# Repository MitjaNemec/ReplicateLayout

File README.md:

# KiCAD Replicate Layout Plugin

> [!NOTE]
> This change ports the plugin to **KiCad 10** (targets KiCad 10.0). KiCad 10
> removed the `pcbnew.ID_V_TOOLBAR` constant the dialog relied on, which made the
> plugin raise on every run (issue #87); this is fixed with a fallback that still
> works on KiCad 9. It has been verified to reproduce the KiCad 9 behaviour exactly
> (see *Testing* below). Similar functionality is also available in KiCad natively;
> see the [official KiCad multichannel documentation](https://docs.kicad.org/10.0/en/pcbnew/pcbnew.html#multichannel).
> The plugin remains useful for replication driven by hierarchical sheets.

The repository includes code for KiCad Action plugin which replicates part of the PCB layout.

Replicate the PCB layout of one hierarchical sheet to other hierarchical sheets. This replication is based upon hierarchical sheets in Eeschema. The basic requirement for replication is that the section to be replicated (source) is completely contained within a single hierarchical sheet, and replicated sections (destination) are just copies of the same sheet. Complex hierarchies are supported and the replicated sheet can contain subsheets. The plugin replicates footprints, zones, tracks, text and drawings.

After the section for replication (source section) has been laid out (footprints, tracks, text objects and zones placed) you need to:
1. Place the anchor footprints for the destination sections you want to replicate. This defines the position and orientation of replicated sections. You can use [the PlaceFootprints action plugin](https://github.com/MitjaNemec/PlaceFootprints) for this.
2. Select the same anchor footprint within the source section.
3. Run the plugin.
4. Choose which hierarchical level you wish to replicate.
5. Select which sheets you want to replicate (default is all of them).
6. Select whether you want to also replicate tracks, zones and/or text objects.
7. Select whether you want to group replicated footprints/tracks/zones/text/drawings by hierarchical sheets.
8. Select whether you want to replicate tracks/zones/text which intersect the pivot bounding box or just those contained within the bounding box.
9. Select whether you want to delete already laid out tracks/zones/text (this is useful when updating an already replicated layout).
10. Hit OK.

By default, only objects which are fully contained in the bounding box constituted by all the footprints in the section will be replicated. You can select to also replicate zones and tracks which intersect this bounding box. Additionally, tracks, text and zones which are already laid out in the replicated bounding boxes can be removed (useful when updating). Note that bounding boxes are squares aligned with the x and y axis, regardless of section orientation.

## Installation

The preferred way to install the plugin is via KiCad's Plugin and Content Manager (PCM). Installation on non-networked devices can be done by downloading [the latest release](https://github.com/MitjaNemec/ReplicateLayout/releases/latest) and installing in the PCM using the `Install from file` option.

## Testing

The plugin ships with a headless, GUI-free test-suite driven entirely through the
pcbnew scripting API (`test_replicate_layout.py`). It runs a number of replication
scenarios (inner/outer hierarchy levels, flipped anchors, "contained" vs.
"intersecting" selection, removal of existing copper, grouping and footprint-text
replication), plus regression tests for issue #86 (already-grouped destination
footprints). Each replication result is checked for **geometric correctness**:
every replicated section must keep the same internal geometry (pairwise distances,
relative orientation and relative flip) as the source section. This check is
independent of any coordinate convention, so it validates the result on its own
merits.

Run it with the Python interpreter bundled with KiCad, for example on macOS:

```bash
/Applications/KiCad/KiCad.app/Contents/Frameworks/Python.framework/Versions/3.9/bin/python3.9 test_replicate_layout.py
```

The suite can additionally compare output against committed reference signatures to
prove byte-for-byte parity with a previous KiCad version: run with `--gen-refs`
under that KiCad (writing `test_refs/*.json`), then a normal run under the new KiCad
verifies the output matches. This is how the KiCad 9 → 10 parity was confirmed.

**Author :** doc.dr. Mitja Nemec
**KiCad 10 port :** 2026
**Date :** 2025

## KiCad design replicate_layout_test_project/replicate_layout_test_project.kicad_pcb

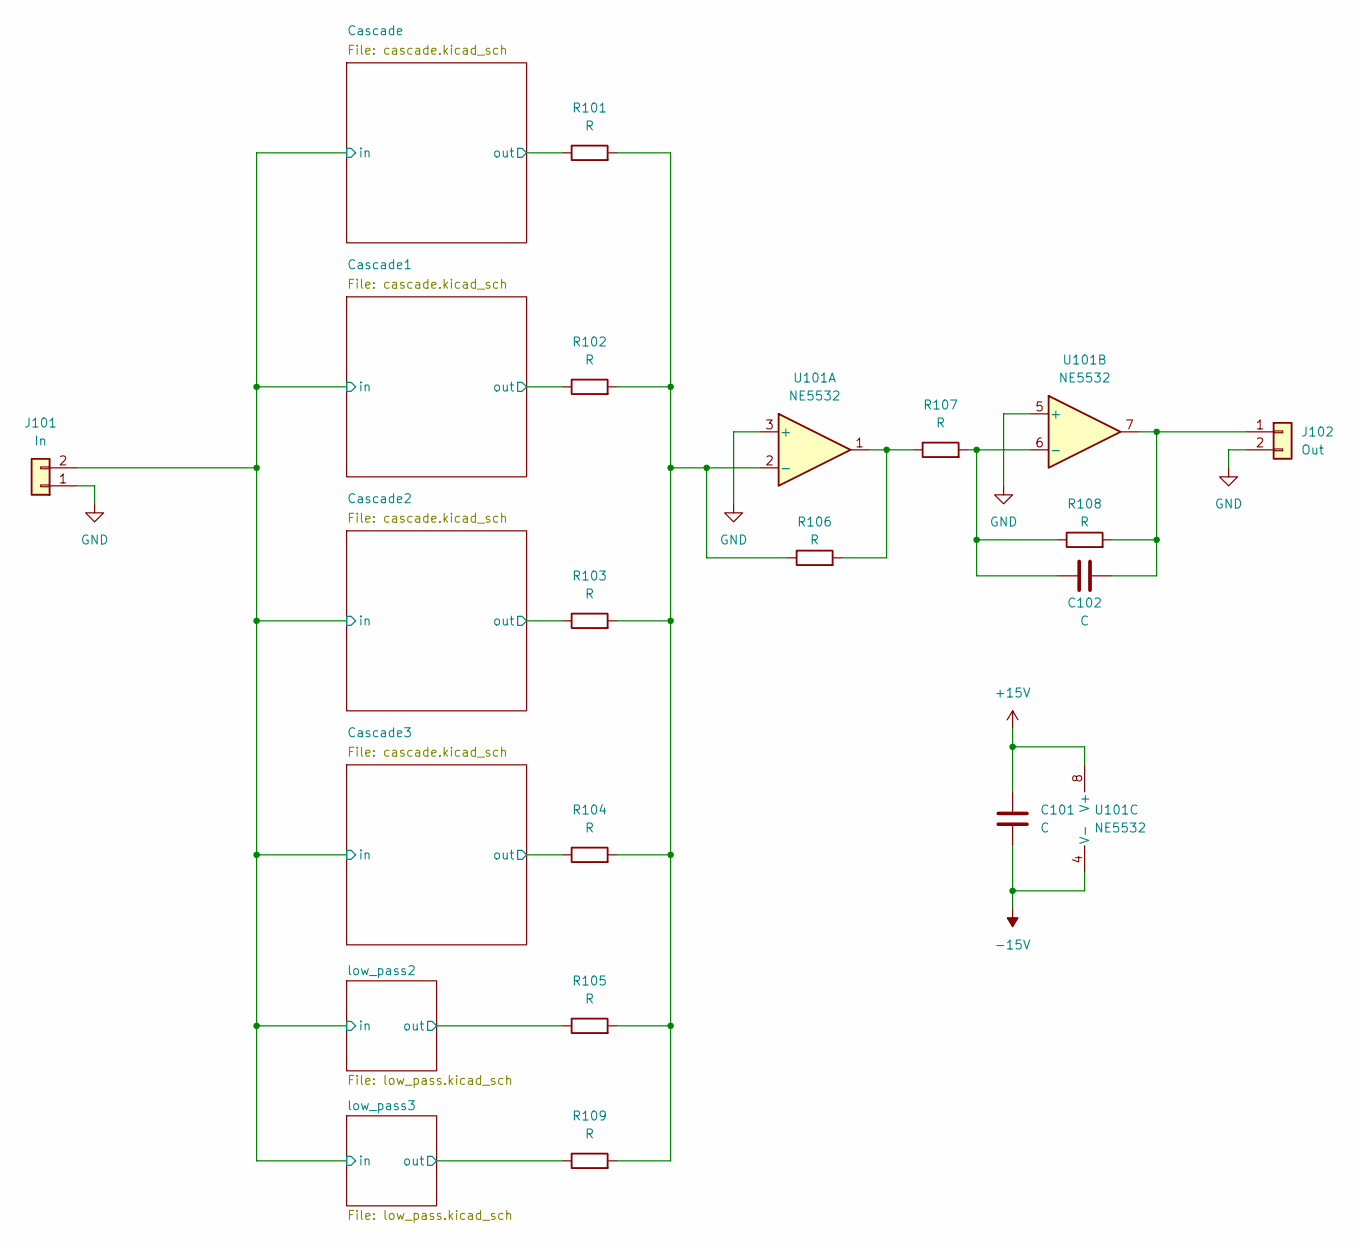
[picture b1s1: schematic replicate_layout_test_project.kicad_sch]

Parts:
C101, C102: C; C_1206_3216Metric
J101: In; PinHeader_1x02_P2.54mm_Vertical
J102: Out; PinHeader_1x02_P2.54mm_Vertical
R101, R102, R103, R104, R105, R106, R107, R108, R109: R; R_1206_3216Metric
U101: NE5532; SOIC-8_5.23x5.23mm_P1.27mm

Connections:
+15V: C101.1, U101.8 (V+); also elsewhere on the board
-15V: C101.2, U101.4 (V-); also elsewhere on the board
/Cascade1/out: R102.1; also elsewhere on the board
/Cascade2/out: R103.1; also elsewhere on the board
/Cascade3/out: R104.1; also elsewhere on the board
/Cascade/in: J101.2; also elsewhere on the board
/Cascade/out: R101.1; also elsewhere on the board
/low_pass2/out: R105.1; also elsewhere on the board
/low_pass3/out: R109.1; also elsewhere on the board
GND: J101.1, J102.2, U101.3 (+), U101.5 (+); also elsewhere on the board
unnamed: C102.1, J102.1, R108.2, U101.7
unnamed: R106.2, R107.1, U101.1
unnamed: R101.2, R102.2, R103.2, R104.2, R105.2, R106.1, R109.2, U101.2 (-)
unnamed: C102.2, R107.2, R108.1, U101.6 (-)

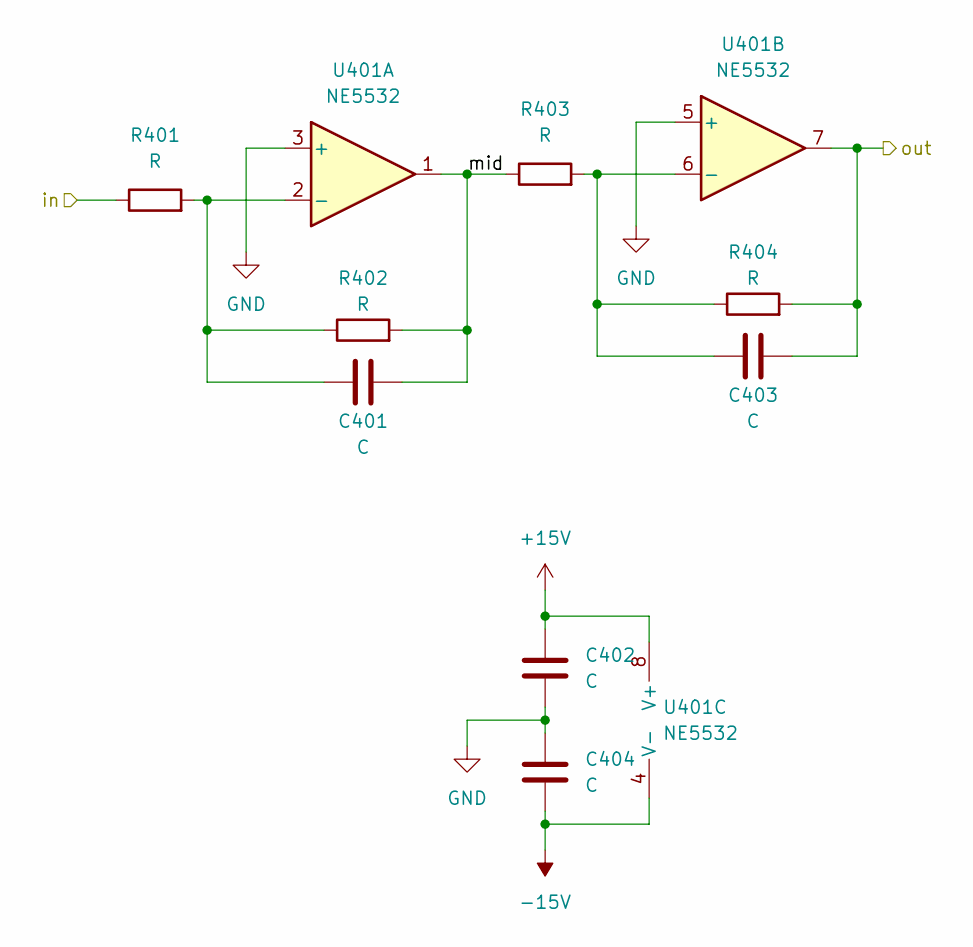
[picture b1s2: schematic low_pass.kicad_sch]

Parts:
C401, C402, C403, C404: C; C_1206_3216Metric
R401, R402, R403, R404: R; R_1206_3216Metric
U401: NE5532; SOIC-8_5.23x5.23mm_P1.27mm

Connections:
+15V: C402.1, U401.8 (V+); also elsewhere on the board
-15V: C404.2, U401.4 (V-); also elsewhere on the board
/Cascade/low_pass1/mid: C401.1, R402.2, R403.1, U401.1
/Cascade/low_pass/out: R401.1; also elsewhere on the board
/Cascade/out: C403.1, R404.2, U401.7; also elsewhere on the board
GND: C402.2, C404.1, U401.3 (+), U401.5 (+); also elsewhere on the board
unnamed: C401.2, R401.2, R402.1, U401.2 (-)
unnamed: C403.2, R403.2, R404.1, U401.6 (-)

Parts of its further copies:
C701, C702, C703, C704, C801, C802, C803, C804, C901, C902, C903, C904, C1001, C1002, C1003, C1004, C1101, C1102, C1103, C1104, C1201, C1202, C1203, C1204, C1301, C1302, C1303, C1304, C1401, C1402, C1403, C1404, C1501, C1502, C1503, C1504: C; C_1206_3216Metric
R701, R702, R703, R704, R801, R802, R803, R804, R901, R902, R903, R904, R1001, R1002, R1003, R1004, R1101, R1102, R1103, R1104, R1201, R1202, R1203, R1204, R1301, R1302, R1303, R1304, R1401, R1402, R1403, R1404, R1501, R1502, R1503, R1504: R; R_1206_3216Metric
U701, U801, U901, U1001, U1101, U1201, U1301, U1401, U1501: NE5532; SOIC-8_5.23x5.23mm_P1.27mm

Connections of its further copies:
+15V: C702.1, C802.1, C902.1, C1002.1, C1102.1, C1202.1, C1302.1, C1402.1, C1502.1, U701.8 (V+), U801.8 (V+), U901.8 (V+), U1001.8 (V+), U1101.8 (V+), U1201.8 (V+), U1301.8 (V+), U1401.8 (V+), U1501.8 (V+); also elsewhere on the board
-15V: C704.2, C804.2, C904.2, C1004.2, C1104.2, C1204.2, C1304.2, C1404.2, C1503.2, U701.4 (V-), U801.4 (V-), U901.4 (V-), U1001.4 (V-), U1101.4 (V-), U1201.4 (V-), U1301.4 (V-), U1401.4 (V-), U1501.4 (V-); also elsewhere on the board
/Cascade1/low_pass1/mid: C901.1, R902.2, R903.1, U901.1
/Cascade1/low_pass/mid: C801.1, R802.2, R803.1, U801.1
/Cascade1/low_pass/out: C803.1, R804.2, R901.1, U801.7
/Cascade1/out: C903.1, R904.2, U901.7; also elsewhere on the board
/Cascade2/low_pass1/mid: C1101.1, R1102.2, R1103.1, U1101.1
/Cascade2/low_pass/mid: C1001.1, R1002.2, R1003.1, U1001.1
/Cascade2/low_pass/out: C1003.1, R1004.2, R1101.1, U1001.7
/Cascade2/out: C1103.1, R1104.2, U1101.7; also elsewhere on the board
/Cascade3/low_pass1/mid: C1301.1, R1302.2, R1303.1, U1301.1
/Cascade3/low_pass/mid: C1201.1, R1202.2, R1203.1, U1201.1
/Cascade3/low_pass/out: C1203.1, R1204.2, R1301.1, U1201.7
/Cascade3/out: C1303.1, R1304.2, U1301.7; also elsewhere on the board
/Cascade/in: R701.1, R801.1, R1001.1, R1201.1, R1401.1, R1501.1; also elsewhere on the board
/Cascade/low_pass/mid: C701.1, R702.2, R703.1, U701.1
/Cascade/low_pass/out: C703.1, R704.2, U701.7; also elsewhere on the board
/low_pass2/mid: C1401.1, R1402.2, R1403.1, U1401.1
/low_pass2/out: C1403.1, R1404.2, U1401.7; also elsewhere on the board
/low_pass3/mid: C1501.1, R1502.2, R1503.1, U1501.1
/low_pass3/out: C1504.1, R1504.2, U1501.7; also elsewhere on the board
GND: C702.2, C704.1, C802.2, C804.1, C902.2, C904.1, C1002.2, C1004.1, C1102.2, C1104.1, C1202.2, C1204.1, C1302.2, C1304.1, C1402.2, C1404.1, C1502.2, C1503.1, U701.3 (+), U701.5 (+), U801.3 (+), U801.5 (+), U901.3 (+), U901.5 (+), U1001.3 (+), U1001.5 (+), U1101.3 (+), U1101.5 (+), U1201.3 (+), U1201.5 (+), U1301.3 (+), U1301.5 (+), U1401.3 (+), U1401.5 (+), U1501.3 (+), U1501.5 (+); also elsewhere on the board
unnamed: C701.2, R701.2, R702.1, U701.2 (-)
unnamed: C703.2, R703.2, R704.1, U701.6 (-)
unnamed: C801.2, R801.2, R802.1, U801.2 (-)
unnamed: C803.2, R803.2, R804.1, U801.6 (-)
unnamed: C901.2, R901.2, R902.1, U901.2 (-)
unnamed: C903.2, R903.2, R904.1, U901.6 (-)
unnamed: C1001.2, R1001.2, R1002.1, U1001.2 (-)
unnamed: C1003.2, R1003.2, R1004.1, U1001.6 (-)
unnamed: C1101.2, R1101.2, R1102.1, U1101.2 (-)
unnamed: C1103.2, R1103.2, R1104.1, U1101.6 (-)
unnamed: C1201.2, R1201.2, R1202.1, U1201.2 (-)
unnamed: C1203.2, R1203.2, R1204.1, U1201.6 (-)
unnamed: C1301.2, R1301.2, R1302.1, U1301.2 (-)
unnamed: C1303.2, R1303.2, R1304.1, U1301.6 (-)
unnamed: C1401.2, R1401.2, R1402.1, U1401.2 (-)
unnamed: C1403.2, R1403.2, R1404.1, U1401.6 (-)
unnamed: C1501.2, R1501.2, R1502.1, U1501.2 (-)
unnamed: C1504.2, R1503.2, R1504.1, U1501.6 (-)

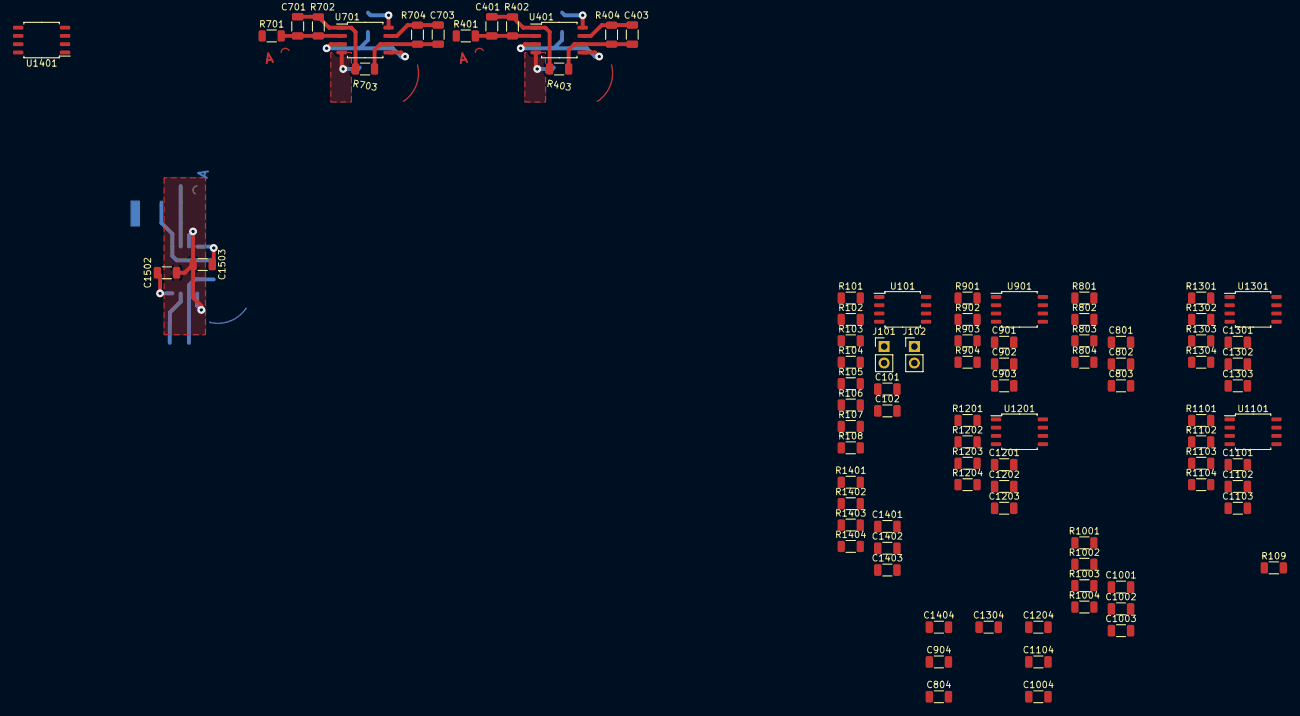
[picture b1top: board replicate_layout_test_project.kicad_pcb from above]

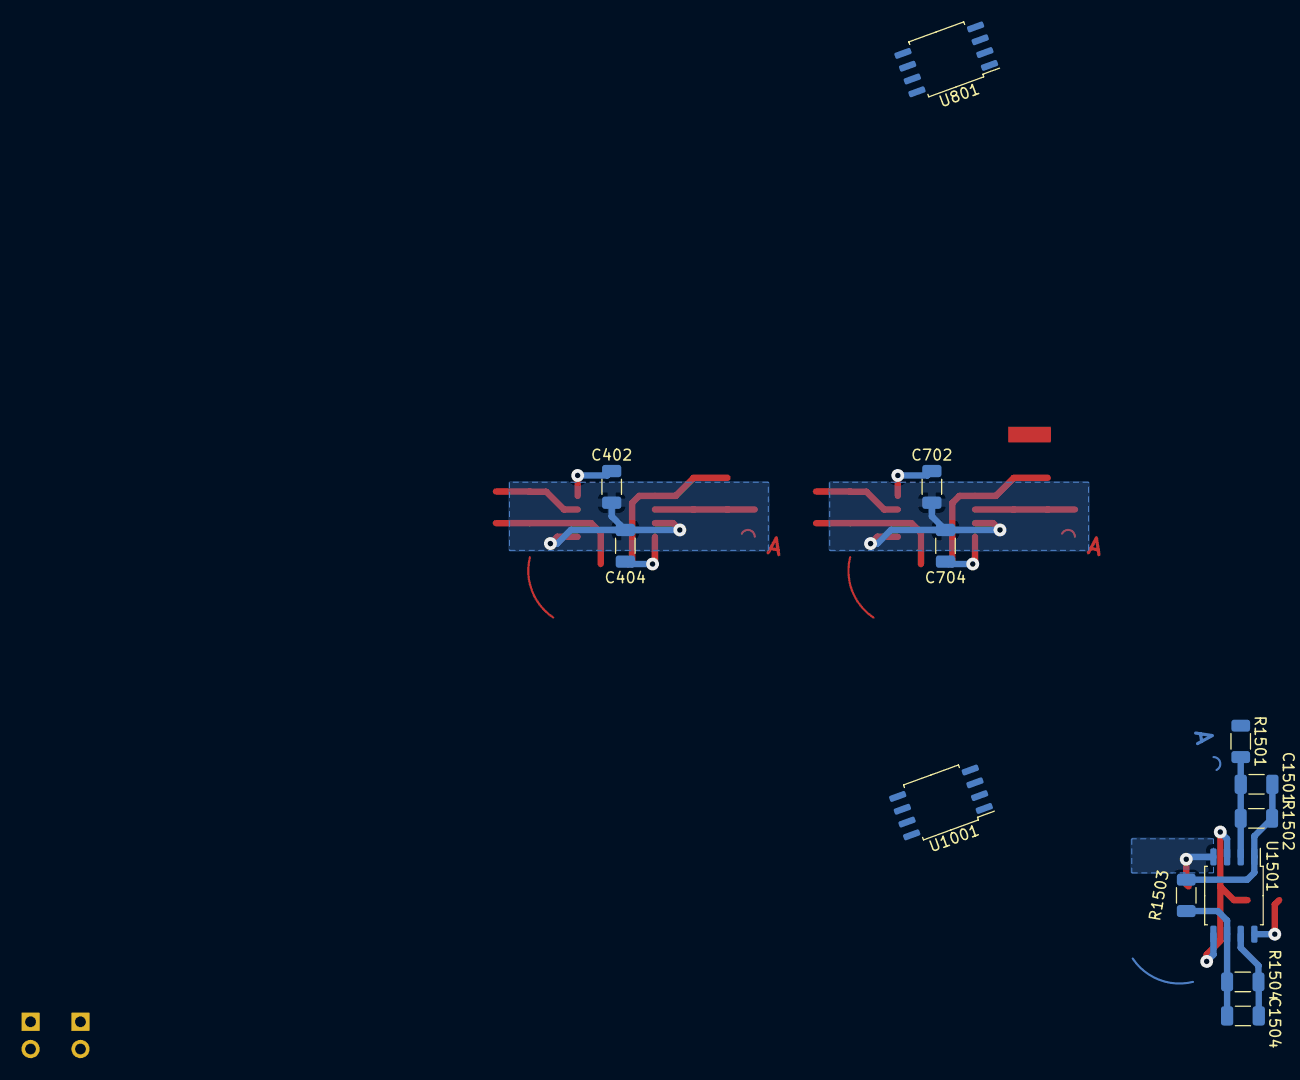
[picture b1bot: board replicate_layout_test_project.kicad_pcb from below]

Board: 2 copper layers, 104 parts (13 on the bottom side), 48 nets.

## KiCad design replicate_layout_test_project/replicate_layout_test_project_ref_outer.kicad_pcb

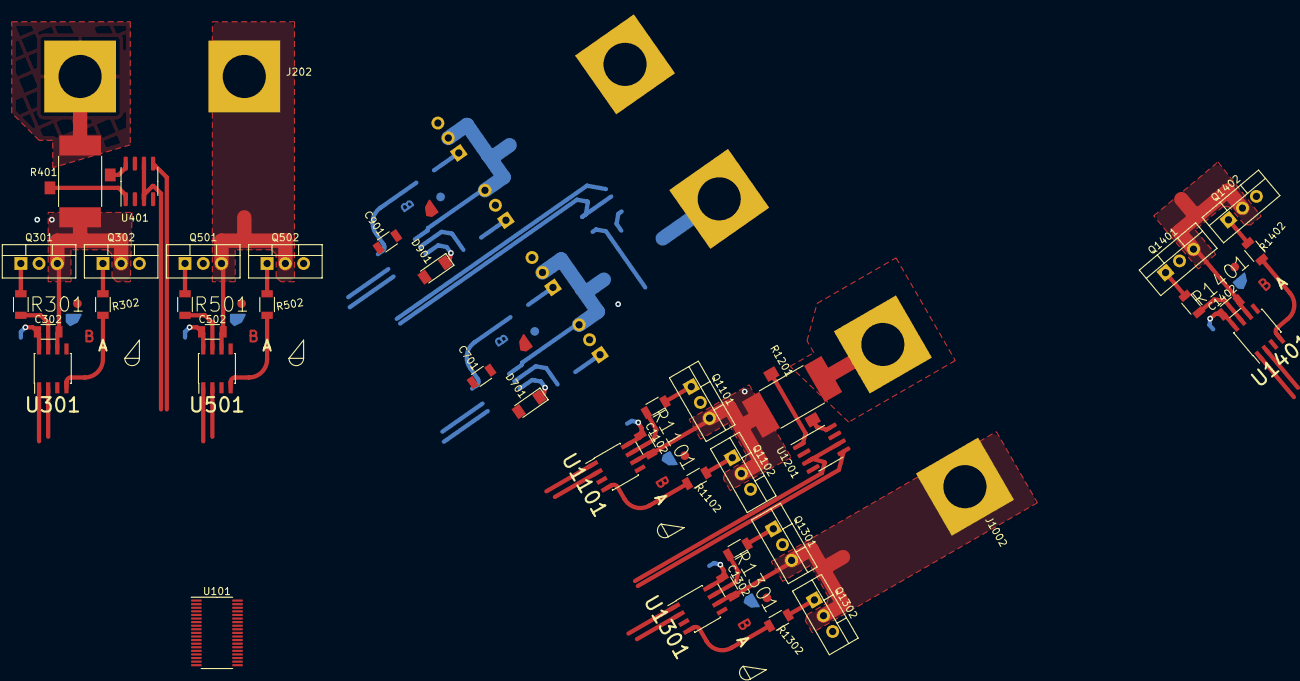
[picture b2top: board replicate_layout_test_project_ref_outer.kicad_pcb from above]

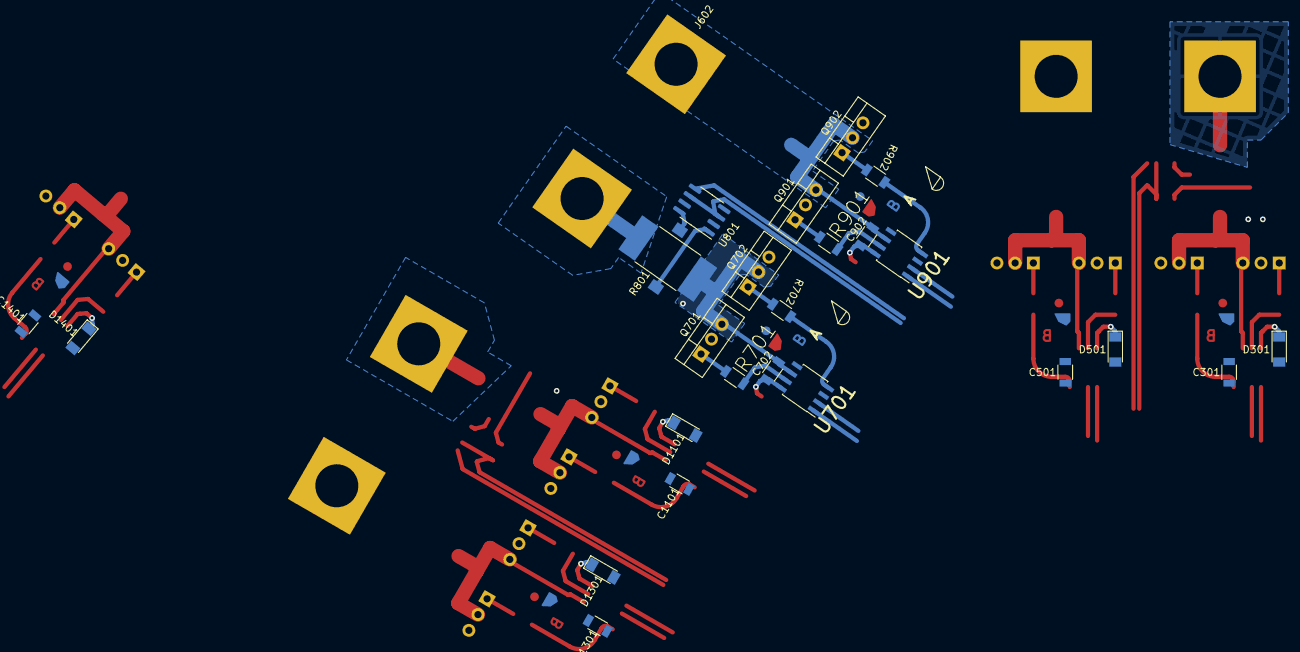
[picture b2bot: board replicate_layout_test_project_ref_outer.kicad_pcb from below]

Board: 2 copper layers, 69 parts (26 on the bottom side), 66 nets.

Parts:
C301, C302, C501, C502, C701, C702, C901, C902, C1101, C1102, C1301, C1302, C1401, C1402: 1u; C1206M
D301, D501, D701, D901, D1101, D1301, D1401: 1N4148; D_MiniMELF
J201, J202, J601, J602, J1001, J1002: Pusa_6mm
Q301, Q302, Q501, Q502, Q701, Q702, Q901, Q902, Q1101, Q1102, Q1301, Q1302, Q1401, Q1402: CSD19531KCS; TO-220
R301, R302, R501, R502, R701, R702, R901, R902, R1101, R1102, R1301, R1302, R1401, R1402: 20R; R1206M
R401, R801, R1201: R_Shunt; RM
U101: TMS320F28027DA; TSSOP-38_4.4x9.7mm_P0.5mm
U301, U501, U701, U901, U1101, U1301, U1401: IR2181; SO8
U401, U801, U1201: INA240A1D; SOIC-8_3.9x4.9mm_P1.27mm

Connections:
+3V3: U101.4 (VDDIO), U101.22 (VDDA), U401.3 (REF2), U401.6 (V+), U801.3 (REF2), U801.6 (V+), U1201.3 (REF2), U1201.6 (V+)
+15V: C301.1, C501.1, C701.1, C901.1, C1101.1, C1301.1, C1401.1, D301.2 (A), D501.2 (A), D701.2 (A), D901.2 (A), D1101.2 (A), D1301.2 (A), D1401.2 (A), U301.5 (VCC), U501.5 (VCC), U701.5 (VCC), U901.5 (VCC), U1101.5 (VCC), U1301.5 (VCC), U1401.5 (VCC)
+VDC: Q301.2 (D), Q501.2 (D), Q701.2 (D), Q901.2 (D), Q1101.2 (D), Q1301.2 (D), Q1401.2 (D)
/Full Bridge1/Current sensor/OUT: J601.1, R801.1
/Full Bridge1/Leg+/VB: C702.1, D701.1 (K), U701.8 (VB)
/Full Bridge1/Leg+/VS: C702.2, Q701.3 (S), Q702.2 (D), R801.4, U701.6 (VS)
/Full Bridge1/Leg-/VB: C902.1, D901.1 (K), U901.8 (VB)
/Full Bridge1/Leg-/VS: C902.2, J602.1, Q901.3 (S), Q902.2 (D), U901.6 (VS)
/Full Bridge1/Q_high: U101.5 (GPIO2/EPWM2A), U701.1 (HIN), U901.2 (LIN)
/Full Bridge1/Q_low: U101.6 (GPIO3/EPWM2B), U701.2 (LIN), U901.1 (HIN)
/Full Bridge1/current: U101.20 (ADCINA2/COMP1A/AIO2), U801.5
/Full Bridge2/Current sensor/OUT: J1001.1, R1201.1
/Full Bridge2/Leg+/VB: C1102.1, D1101.1 (K), U1101.8 (VB)
/Full Bridge2/Leg+/VS: C1102.2, Q1101.3 (S), Q1102.2 (D), R1201.4, U1101.6 (VS)
/Full Bridge2/Leg-/VB: C1302.1, D1301.1 (K), U1301.8 (VB)
/Full Bridge2/Leg-/VS: C1302.2, J1002.1, Q1301.3 (S), Q1302.2 (D), U1301.6 (VS)
/Full Bridge2/Q_high: U101.7 (GPIO4/EPWM3A), U1101.1 (HIN), U1301.2 (LIN)
/Full Bridge2/Q_low: U101.8 (GPIO5/EPWM3B/ECAP1), U1101.2 (LIN), U1301.1 (HIN)
/Full Bridge2/current: U101.21 (ADCINA0/VREFHI), U1201.5
/Full Bridge/Current sensor/OUT: J201.1, R401.1
/Full Bridge/Leg+/VB: C302.1, D301.1 (K), U301.8 (VB)
/Full Bridge/Leg+/VS: C302.2, Q301.3 (S), Q302.2 (D), R401.4, U301.6 (VS)
/Full Bridge/Leg-/VB: C502.1, D501.1 (K), U501.8 (VB)
/Full Bridge/Leg-/VS: C502.2, J202.1, Q501.3 (S), Q502.2 (D), U501.6 (VS)
/Full Bridge/Q_high: U101.37 (GPIO0/EPWM1A), U301.1 (HIN), U501.2 (LIN)
/Full Bridge/Q_low: U101.36 (GPIO1/EPWM1B/COMP1OUT), U301.2 (LIN), U501.1 (HIN)
/Full Bridge/current: U101.19 (ADCINA4/AIO4), U401.5
/Leg+1/Q_HIGH: U101.9 (GPIO6/EPWM4A/EPWMSYNCI/EPWMSYNCO), U1401.1 (HIN)
/Leg+1/Q_LOW: U101.10 (GPIO7/EPWM4B/SCIRXDA), U1401.2 (LIN)
/Leg+1/VB: C1402.1, D1401.1 (K), U1401.8 (VB)
/Leg+1/VS: C1402.2, Q1401.3 (S), Q1402.2 (D), U1401.6 (VS)
GND: C301.2, C501.2, C701.2, C901.2, C1101.2, C1301.2, C1401.2, Q302.3 (S), Q502.3 (S), Q702.3 (S), Q902.3 (S), Q1102.3 (S), Q1302.3 (S), Q1402.3 (S), U101.2 (VSS), U101.12 (VSS), U101.23 (VSSA/VREFLO), U301.3 (COM), U401.2 (GND), U401.4 (GND), U401.7 (REF1), U501.3 (COM), U701.3 (COM), U801.2 (GND), U801.4 (GND), U801.7 (REF1), U901.3 (COM), U1101.3 (COM), U1201.2 (GND), U1201.4 (GND), U1201.7 (REF1), U1301.3 (COM), U1401.3 (COM)
unnamed: Q301.1 (G), R301.2
unnamed: Q302.1 (G), R302.2
unnamed: Q501.1 (G), R501.2
unnamed: Q502.1 (G), R502.2
unnamed: Q701.1 (G), R701.2
unnamed: Q702.1 (G), R702.2
unnamed: Q901.1 (G), R901.2
unnamed: Q902.1 (G), R902.2
unnamed: Q1101.1 (G), R1101.2
unnamed: Q1102.1 (G), R1102.2
unnamed: Q1301.1 (G), R1301.2
unnamed: Q1302.1 (G), R1302.2
unnamed: Q1401.1 (G), R1401.2
unnamed: Q1402.1 (G), R1402.2
unnamed: R301.1, U301.7 (HO)
unnamed: R302.1, U301.4 (LO)
unnamed: R401.2, U401.8 (+)
unnamed: R401.3, U401.1 (-)
unnamed: R501.1, U501.7 (HO)
unnamed: R502.1, U501.4 (LO)
unnamed: R701.1, U701.7 (HO)
unnamed: R702.1, U701.4 (LO)
unnamed: R801.2, U801.8 (+)
unnamed: R801.3, U801.1 (-)
unnamed: R901.1, U901.7 (HO)
unnamed: R902.1, U901.4 (LO)
unnamed: R1101.1, U1101.7 (HO)
unnamed: R1102.1, U1101.4 (LO)
unnamed: R1201.2, U1201.8 (+)
unnamed: R1201.3, U1201.1 (-)
unnamed: R1301.1, U1301.7 (HO)
unnamed: R1302.1, U1301.4 (LO)
unnamed: R1401.1, U1401.7 (HO)
unnamed: R1402.1, U1401.4 (LO)

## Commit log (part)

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2022-01-18 Partialy tested plugin
2022-01-19 Added test project
2022-01-19 Replikacija zrcaljenih dizajnov dela
2022-01-20 Towards flip replication
2022-01-21 txt_position correct, only orientation to solve
2022-01-21 Solved fp_text replication
2022-01-22 text replication solved for fliped replication
2022-01-25 flipped fp position should work now
2022-01-26 Fixed flipped text position and orientation
2022-01-26 fixed flipped and normal replication
2022-01-27 slight refactoring
2022-01-27 Added support for replicating grouped items only
2022-01-28 Dodal testne datoteke
2022-01-28 Minor changes, prepared for first release
2022-01-31 Fix wx frame parent search for macOs
2022-02-03 Don't delete tracks outside bounding box if on common nets
    Fixes #2
2022-02-03 Remove .kicad_prl
    Fixes #3
2022-02-09 Solve the wx frame handle issue
2022-02-19 Fix a bug when layout only footprints are present
2022-02-21 Implement dynamic feedback which items will be replicated
2022-04-13 Add README.md
2022-05-14 Fix footprint positing for v6.99
    Fix footprint and text positing for v6.99, still missing tracks
2022-05-14 Fix typo
2022-05-14 Simplify some code
2022-05-15 Fix track angle
    Fix track angle replication as discussion in https://forum.kicad.info/t/fixing-action-plugin-error-to-rotate-a-track/35730
2022-05-15 Fix get angles
2022-05-18 Minor logic bugfixes: - Keep destination sheet selection when changing settings - Replicate tracks which are completely local to source sheet even if they are outside of bounding box - update test co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
2022-05-23 Clear highlight before running the plugin so that duplicated items don't stay higlighted
2022-05-23 bump version
2022-06-27 Add default level selection
2022-08-06 Add an option to leave alone locked items
    Fixes #17
2022-08-08 Dodal zaklenjen tekst
2022-10-10 add gitattributes to forse lf line endings
2022-10-26 Improve error dialog
2022-10-30 fixed releases link in README.md
2022-11-14 Significant refactoring of item selection code, expand selection to outside sheet items which are within src group
2022-11-15 Bump version.txt
2022-11-16 update .gitignore, remove item selection/filtering from replication code
2022-11-24 Fix corner case with nested hierarchy when one of the intermediate levels does not have any symbols/footprints
2022-12-03 Fix settings parsing, ReplicateLayoutDialog.on_ok(), Replicator.replicate_layout()
2022-12-04 additional bugfixes
2022-12-14 Improve error messages that user sees
2022-12-17 change lstrip to replace (lstrip produce bug). Use upper function in sheet_id (sometimes sheet_id is not uppercase. And check only sheet filename for searching duplicate footprints (previous code not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
2022-12-22 Fix the initial design check bug, refactor #30, log the zone replication cas where sour zone net is not found in netpairs list.
    Fixes #32
2022-12-30 undo debugging changes
2022-12-30 Bump version and change metadata to bind to kicad version
2023-01-04 fixed encoding issue
2023-01-04 adding box2i from rect
2023-01-04 fixed spacing in the regex
2023-01-05 Add forgoten V5 porting code to schematic parsing code. Enforce utf-8 encoding when reading schematics files.
    Fixes #34
    Fixes #33
2023-01-05 Fix a type in the error message
2023-01-05 Properly invert the locked item UI (so it is consistent with code)
2023-01-05 Encoding fix, proper angle handling in degrees, fixed a couple of typos
2023-01-10 it at least moves components now but doesn't place traces
2023-01-20 Remove hyperlinkctrl from GUI
2023-01-23 Revert removal of wxhyperlinkctrl
2023-01-23 Revert removal of wxhyperlinkctrl, make footprint parsing more robust, add logging to netpairs search
2023-01-24 use proper information for center of text and center of footprint when positioning footprint text.
    Fixes #35
2023-01-27 added logging on pad sorting
2023-02-19 Add connectivity issue test and dialog, refactor net_pairs(),
2023-02-19 Add connectivity check and warning, refactor net_pairs()
2023-02-21 schematics file parsing bugfix
2023-02-23 Add conn_issue_GUI to the package
2023-03-01 connectivity test bugfix
2023-03-01 Added logging
2023-03-19 Expand net pair matching code
2023-03-19 import V7 fixes (net pair code, GUI text corrections
2023-04-03 Better schematics filename handling
2023-04-19 Fix typo in README
2023-04-19 Add README link to PlaceFootprints plugin
2023-04-19 README wording and grammar tweaks
2023-04-24 README wording and grammar tweaks
    (cherry picked from commit be4ff601e2aff1e4ceebd193f608ff48d6774192)
2023-04-24 Fix typo in README
    (cherry picked from commit 9598200e13a66653d25929f957b6e1170fd9b6e4)
2023-04-24 Add README link to PlaceFootprints plugin
    (cherry picked from commit 05fa603c8ed3f1af7b1a4c9f59bd68c675016c16)
2023-05-14 Duplicate tracks, vias, zones, drawings in v7
2023-05-17 Add call to Cast when invoking Duplicate method to solve the 7.0.2 bug
2023-05-18 Fix a syntax error
2023-05-31 Add grouping replicated items
2023-05-31 Fixed typo
2023-06-02 GUI layout changes
2023-06-02 Slight refactoring of the destination grouping feature
2023-06-02 version bump
2023-06-05 Change exotic connectivity test and handling (do the replication and just let the user know that we've detected possible issues)
2023-06-05 UX improvements
2023-06-06 Add test for existing groups and footprint membership in groups
2023-06-19 Fix grouping issue
    Fixes #58
2023-06-22 Fix getting items from namesake groups
2023-11-20 Fix v7.99
2024-01-09 Fix footprint text rotation
2024-01-11 updated test project
2024-01-12 updated schematics parsing code, add support for connected drawings
2024-01-12 update test project
2025-01-29 New KiCAD 9 API
2025-03-16 improve error msg
2025-03-16 update version numbers
2025-04-02 Add deprecation dialog
2025-05-27 Bugfix when plugin can not find matching footprints
2026-04-08 Dodal avtorstvo
    Added author and date information to the README.
2026-04-08 Change date from 2022-2025 to 2025
    Updated the date in the README file to reflect the current year.
2026-05-07 Revise README to reflect plugin status
    Updated README to indicate plugin functionality is now native to KiCad and no longer maintained.
2026-05-29 Port to KiCad 10 and fix grouped-destination crash (#87, #86)
    KiCad 10 support (#87)
    - KiCad 10 removed pcbnew.ID_V_TOOLBAR, which action_replicate_layout.py used
    to position the dialog; the plugin raised on every run. Add get_dialog_position()
    which uses the toolbar id when present (KiCad 9) and otherwise falls back to the
    right edge of the editor frame (KiCad 10).
    - metadata_source.json: kicad_version 10.0 / max 10.99; version.txt -> 5.0.0.
